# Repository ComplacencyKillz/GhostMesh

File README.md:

---
---
# GhostMesh

**A deployable red-team mesh platform — planted sensors, encrypted command-and-control, line-of-sight control, and a destruct — running on nothing the target owns.**

GhostMesh is a **backpack that snaps onto a Flipper Zero — then detaches and stays in the field.** Attached, it turns your Flipper into a long-range mesh radio: messaging and control over LoRa, no phone, no cell, no internet, nothing the target controls. Detached and planted, it becomes an autonomous node — watching its own perimeter, holding its place on the mesh, and taking orders by line-of-sight IR from you or over the encrypted mesh from your team. Drop it, walk away, and it stays yours.

This repository is the **framework** — the sensing, signaling, and command backbone that offensive capability is built on top of. It reports, it takes commands, and it erases itself on capture. Unlicensed by design.

---

## What's Here

Everything to build one, end to end — all of it open source:

| Deliverable | Location | Status |
|-------------|----------|--------|
| **Operator app** — the Flipper FAP (C99) | [<code>flipper-app/</code>](flipper-app/) | working |
| **Backpack firmware** — custom Heltec Meshtastic modules (C++) | [<code>heltec-firmware/</code>](heltec-firmware/) | working |
| **Board CAD** — the GhostMesh PCB | [<code>kicad/</code>](kicad/) | in progress |
| **Case CAD** — 3D-printable enclosure (FreeCAD) | — | planned |
| **Hardware spec** — every component, datasheet-trackable | [<code>docs/hardware.md</code>](docs/hardware.md) | in progress |
| **Wiring schematic** — the full system, end to end | [<code>kicad/</code>](kicad/) · [<code>docs/wiring.md</code>](docs/wiring.md) | in progress |

The two software halves work today. The board is being designed; the case, the finished component spec, and the whole-system schematic follow it. The transmission — [ghostmesh.info](ghostmesh.info/).

---

## How It Works

The backpack is a **shield.** It plugs onto the Flipper Zero's GPIO header, taps the three pins it needs — TX, RX, GND — and passes the header through to the Heltec and sensor stack riding on top. One board. It runs from its own battery; the Flipper runs from its own. The header is the only link, and it's a link you can break on purpose.

<pre><code>
   ATTACHED — comms terminal            DETACHED — planted node
  ┌──────────────────────┐            ┌──────────────────────┐
  │  backpack             │  pull off  │  backpack             │  ))) mesh → teammate's Flipper
  │  Heltec + sensors     │  ───────▶  │  on its own battery   │
  │ ══ GPIO header ══     │  ◀───────  │  sensing · on mesh    │   ~~ IR → your Flipper
  │  Flipper Zero         │  snap on   │                       │
  └──────────────────────┘            └──────────────────────┘
</code></pre>

**Attached — a comms terminal.** The backpack rides on the Flipper, which drives it over the header link: send and receive over the LoRa mesh, read telemetry, work the Control screen. Your handheld is now a long-range, infrastructure-free field radio.

**Detached — a planted node.** Pull the backpack off. The header disconnects; it keeps running on its own battery as an isolated asset — sensing its surroundings, holding its place on the mesh, waiting.

**Controlled from anywhere.**
- The **original operator** reaches the planted node by **line-of-sight IR** — arm, disarm, or fire the destruct without touching it.
- **Teammates** reach it over the **encrypted LoRa mesh** — status, indicators, wipe, from any Flipper on the private channel.

---

## What Works Today

**Operator terminal — Flipper FAP**
- Send / receive text over the mesh; canned message profiles (3 built-in + up to 5 from SD YAML)
- RX history, RSSI / SNR, marquee display, dated CSV logging (→ KML via <code>tools/log_to_kml.py</code>)
- Live telemetry: temperature / humidity / pressure (BME280), GPS position, battery %
- Menu-hub UI with **Control** (IR arm / disarm / wipe), **encrypted config backup**, and a live **Settings** screen

**Web configurator — [ghostmesh.info/config](https://ghostmesh.info/config)** (Chrome/Edge, USB, no install)
- Live node config over Web Serial (<code>/set</code>/<code>/cfg</code>) — every setting as a slider/toggle
- **Firmware flasher** (esptool-js) — flash the latest build or your own <code>.bin</code> from the browser
- **Payload Upload** — <code>/put</code> chunked file transfer to the node's flash, CRC32-verified

**Backpack — custom Heltec firmware**
- Tamper detection: tilt (moved), photoresistor (case opened), ultrasonic proximity (RCWL-1601, approach)
- Arming gate — sensors report only when armed; flipped by a switch, the mesh, or IR
- Indicators: buzzer, vibration motor, RGB status LED (colors + a green↔red gradient)
- Mesh command CLI — <code>/cmd @target</code>: status, arm/disarm, buzz, vibrate, led, fx, <code>/set</code>/<code>/cfg</code>, <code>/put</code>, wipe
- **Configurable everything**: per-command mesh replies on/off, a <code>silent</code> stealth mode (screen + LEDs + buzzer/vibration off), per-sensor battery gating, GPS/telemetry rate control — all live, no reflash
- IR line-of-sight control (NECext): arm / disarm / the <code>ARM → WIPE → CONFIRM</code> destruct
- Destruct: armed-gated **complete flash erase** — firmware, config, and channel keys wiped to USB download mode; recover by reflash + encrypted-backup restore

**Hardware**
- KiCad schematics for the Flipper and Heltec modules (board layout in progress)

Full phase-by-phase status: [<code>docs/roadmap.md</code>](docs/roadmap.md).

---

## What You Need

The **GhostMesh backpack** — the custom board that integrates all of this into one Flipper shield — is under active development ([<code>kicad/</code>](kicad/)). Until it's fabricated, you build on off-the-shelf parts:

**Core — send / receive over the mesh:**
- Flipper Zero
- Heltec WiFi LoRa 32 V3 (ESP32-S3 + SX1262) + a 915 MHz antenna
- A LiPo for the Heltec (independent of the Flipper battery)
- A PINGEQUA protoboard to seat the Heltec on the Flipper's GPIO header — the dev stand-in for the real board, not the product

**Full backpack — sensing + security:** adds a BME280, a GPS module, tilt / photoresistor / proximity sensors, an IR receiver, a buzzer, a vibration motor, and their driver parts.

The complete bill of materials — every component, GPIO, and driver circuit — is in [<code>docs/hardware.md</code>](docs/hardware.md).

---

## Quick Start

### 1. Flash Meshtastic to the Heltec
Visit [flasher.meshtastic.org](https://flasher.meshtastic.org), select **Heltec WiFi LoRa 32 V3**, flash, and set your region. See [<code>docs/meshtastic-setup.md</code>](docs/meshtastic-setup.md) for the private-channel configuration you'll want before any real use.

### 2. Connect the backpack (three signals)
On the backpack PCB these run through the GPIO header automatically. On the bench, jumper them:
<pre><code>
Flipper U_TX (pin 13)  →  Heltec GPIO7  (Serial module RX)
Flipper U_RX (pin 14)  →  Heltec GPIO6  (Serial module TX)
Flipper GND            →  Heltec GND
</code></pre>
Then configure the Meshtastic **Serial module**: PROTO mode, RX 7, TX 6, 115200, override-console OFF. **Not GPIO43/44** — the CP2102 USB bridge clamps those on battery. **Never bridge the power rails** — the backpack and Flipper each run from their own battery. See [<code>docs/wiring.md</code>](docs/wiring.md).

### 3. Build and install the FAP
<pre><code>
pip install ufbt
cd flipper-app
ufbt
</code></pre>
Copy <code>dist/ghostmesh.fap</code> to <code>SD:/apps/Tools/</code> on the Flipper, or <code>ufbt launch</code> over USB. See [<code>docs/flipper-setup.md</code>](docs/flipper-setup.md).

### 4. (Optional) Build the backpack firmware
The custom Heltec modules build on top of stock Meshtastic. See [<code>heltec-firmware/README.md</code>](heltec-firmware/README.md).

### 5. Run
**Apps → Tools → GhostMesh.** The title bar shows <code>...</code> during the handshake (~3 s), then <code>RDY</code>, then the backpack's battery %. You land on the menu hub — Messages, RX History, Sensors, Control, Status, Backup. See [<code>docs/user-guide.md</code>](docs/user-guide.md).

---

## Documentation

**Start here**
- [<code>docs/overview.md</code>](docs/overview.md) — the system end to end: architecture, concepts, the platform vision

**Build & operate**
- [<code>docs/hardware.md</code>](docs/hardware.md) — full BoM, GPIO allocation, power
- [<code>docs/wiring.md</code>](docs/wiring.md) — pinouts, driver circuits, sensor wiring
- [<code>docs/meshtastic-setup.md</code>](docs/meshtastic-setup.md) — Meshtastic config, private channels
- [<code>docs/flipper-setup.md</code>](docs/flipper-setup.md) — ufbt build & install
- [<code>heltec-firmware/README.md</code>](heltec-firmware/README.md) — building the backpack firmware
- [<code>docs/user-guide.md</code>](docs/user-guide.md) — the FAP, screen by screen

**Operate the backpack**
- [<code>docs/command-cli.md</code>](docs/command-cli.md) — the mesh command CLI + wipe safety
- [<code>docs/opsec.md</code>](docs/opsec.md) — encryption, the destruct, stealth, metadata

**Reference**
- [<code>docs/developer-guide.md</code>](docs/developer-guide.md) — architecture, ISR rules, contributing
- [<code>docs/serial-modes.md</code>](docs/serial-modes.md) — PROTO framing & protobuf field numbers
- [<code>docs/roadmap.md</code>](docs/roadmap.md) — the phased plan (Phases 0–14)
- [<code>docs/red-team-lab-use-cases.md</code>](docs/red-team-lab-use-cases.md) — authorized use cases

---

## License

MIT — see [LICENSE](LICENSE).

<pre><code>
// so light your candles
</code></pre>

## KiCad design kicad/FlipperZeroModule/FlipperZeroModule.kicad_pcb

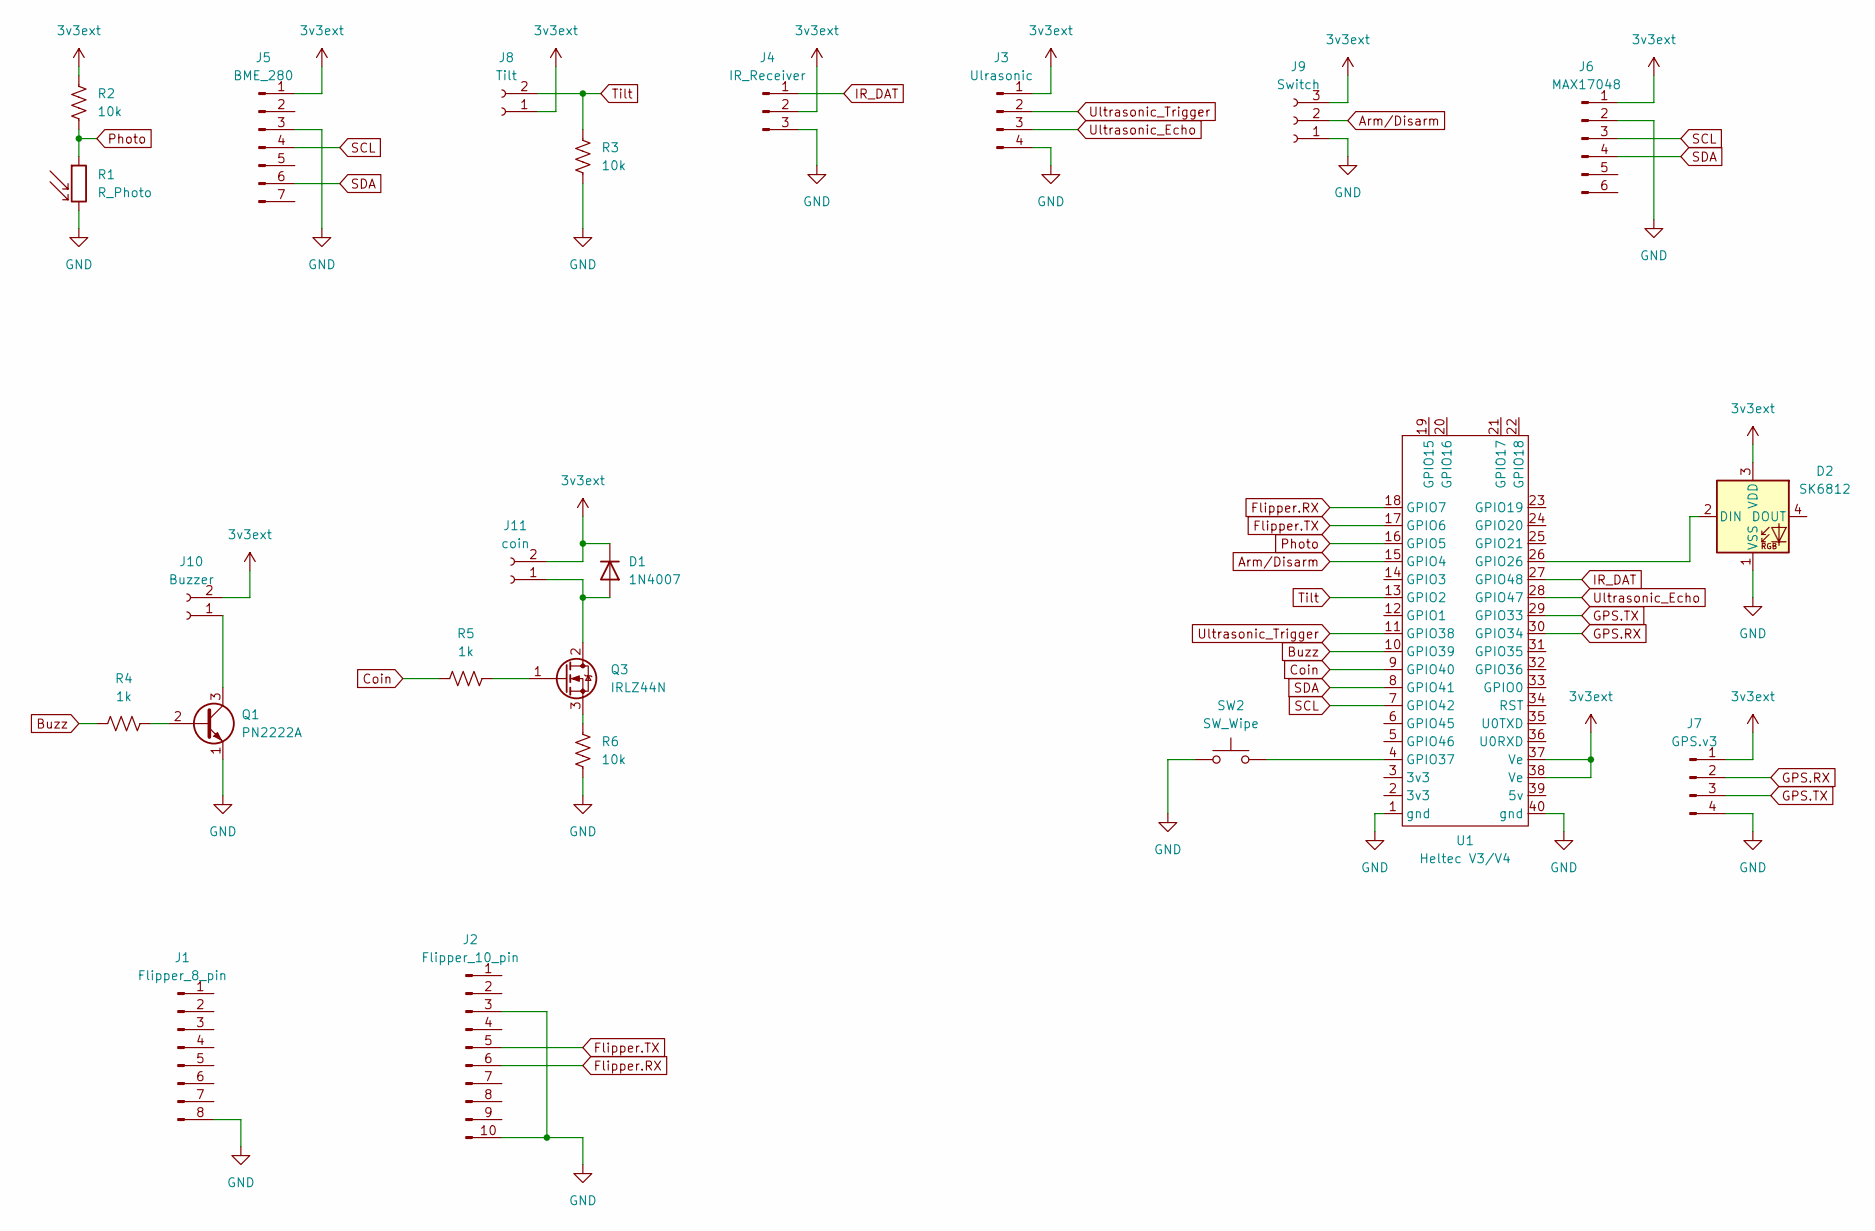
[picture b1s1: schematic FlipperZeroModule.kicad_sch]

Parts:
D1: 1N4007; D_DO-41_SOD81_P10.16mm_Horizontal
D2: SK6812; LED_SK6812_PLCC4_5.0x5.0mm_P3.2mm
J1: Flipper_8_pin; PinHeader_1x08_P2.54mm_Vertical
J2: Flipper_10_pin; PinHeader_1x10_P2.54mm_Vertical
J3: Ulrasonic; PinHeader_1x04_P2.54mm_Vertical
J4: IR_Receiver; PinHeader_1x03_P2.54mm_Vertical
J5: BME_280; PinHeader_1x07_P2.54mm_Vertical
J6: MAX17048; PinHeader_1x06_P2.54mm_Vertical
J7: GPS.v3; PinHeader_1x04_P2.54mm_Vertical
J8: Tilt; PinHeader_1x02_P2.54mm_Vertical
J9: Switch; PinHeader_1x03_P2.54mm_Vertical
J10: Buzzer; PinHeader_1x02_P2.54mm_Vertical
J11: coin; PinHeader_1x02_P2.54mm_Vertical
Q1: PN2222A; TO-92_Inline
Q3: IRLZ44N; TO-220-3_Vertical
R1: R_Photo; R_LDR_5.1x4.3mm_P3.4mm_Vertical
R2, R3, R6: 10k; R_Axial_DIN0207_L6.3mm_D2.5mm_P7.62mm_Horizontal
R4, R5: 1k; R_Axial_DIN0207_L6.3mm_D2.5mm_P7.62mm_Horizontal
SW2: SW_Wipe; SW_PUSH-12mm
U1: Heltec V3/V4; heltech v4

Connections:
3v3ext: D1.1 (K), D2.3 (VDD), J3.1, J4.2, J5.1, J6.1, J7.1, J8.1, J9.3, J10.2, J11.2, R2.1, U1.37 (Ve), U1.38 (Ve)
Arm/Disarm: J9.2, U1.15 (GPIO4)
Buzz: R4.1, U1.10 (GPIO39)
Coin: R5.1, U1.9 (GPIO40)
Flipper.RX: J2.6, U1.18 (GPIO7)
Flipper.TX: J2.5, U1.17 (GPIO6)
GND: D2.1 (VSS), J1.8, J2.3, J2.10, J3.4, J4.3, J5.3, J6.2, J7.4, J9.1, Q1.1 (E), R1.2, R3.2, R6.2, SW2.1, U1.1 (gnd), U1.40 (gnd)
GPS.RX: J7.2, U1.30 (GPIO34)
GPS.TX: J7.3, U1.29 (GPIO33)
IR_DAT: J4.1, U1.27 (GPIO48)
unnamed: D1.2 (A), J11.1, Q3.2 (D)
unnamed: D2.2 (DIN), U1.26 (GPIO26)
unnamed: J10.1, Q1.3 (C)
unnamed: Q1.2 (B), R4.2
unnamed: Q3.1 (G), R5.2
unnamed: Q3.3 (S), R6.1
unnamed: SW2.2, U1.4 (GPIO37)
Photo: R1.1, R2.2, U1.16 (GPIO5)
SCL: J5.4, J6.3, U1.7 (GPIO42)
SDA: J5.6, J6.4, U1.8 (GPIO41)
Tilt: J8.2, R3.1, U1.13 (GPIO2)
Ultrasonic_Echo: J3.3, U1.28 (GPIO47)
Ultrasonic_Trigger: J3.2, U1.11 (GPIO38)

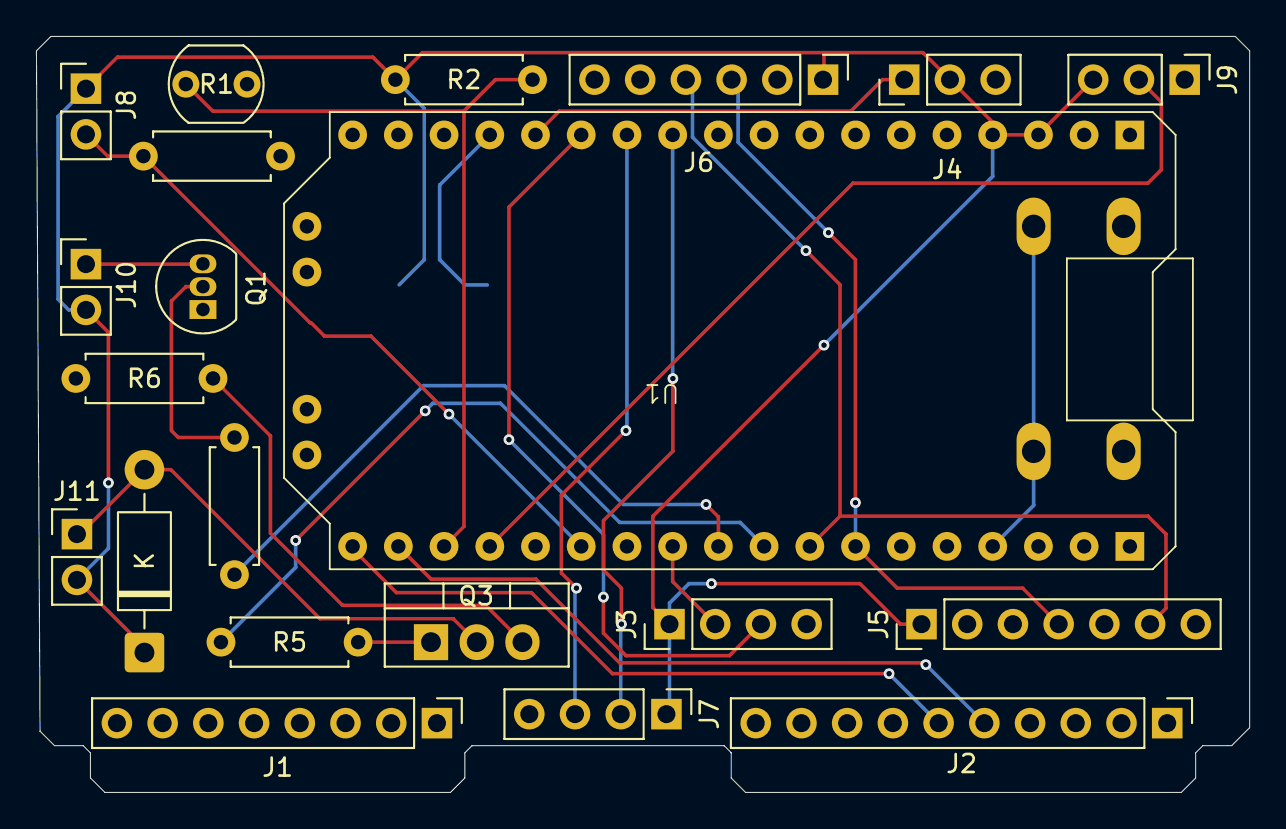
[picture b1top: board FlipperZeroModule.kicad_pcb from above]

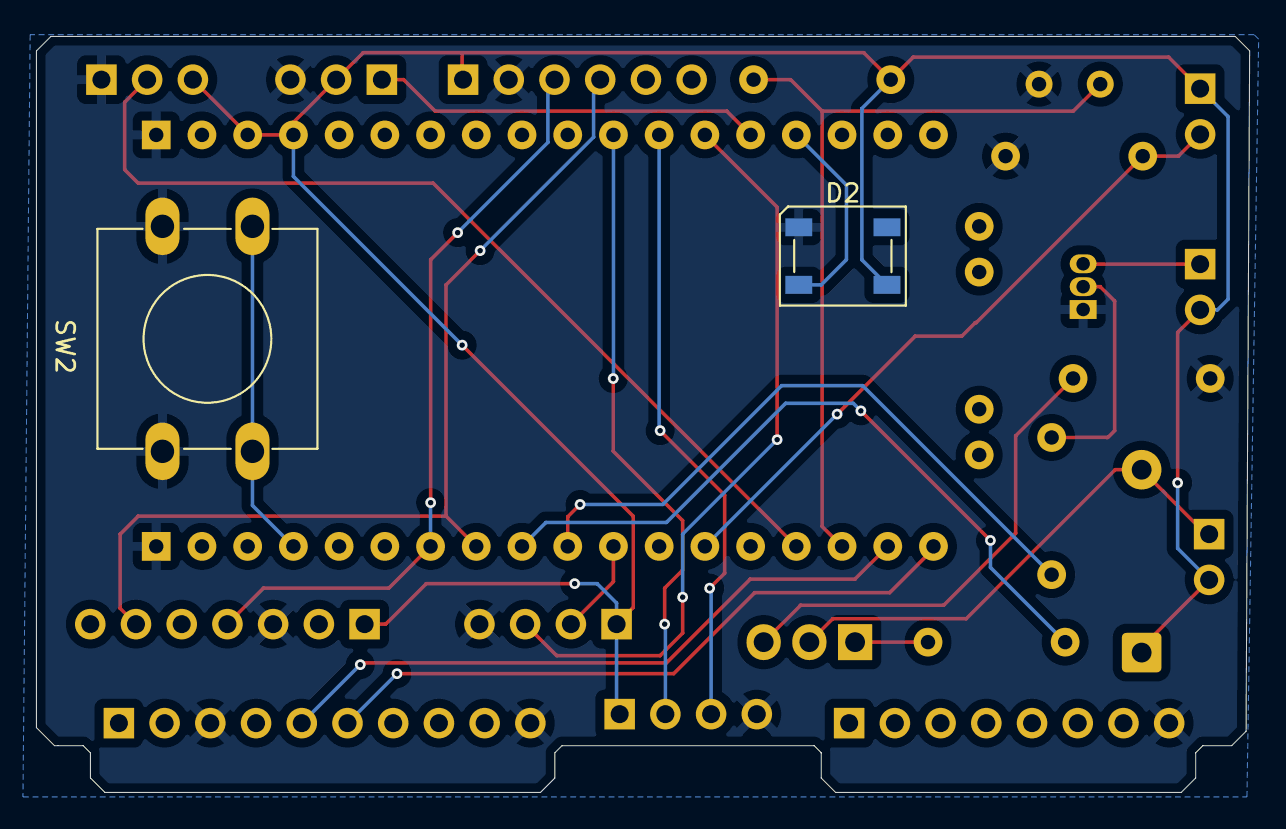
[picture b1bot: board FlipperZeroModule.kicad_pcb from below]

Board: 2 copper layers, 67.4 x 42.0 mm, 23 parts (2 on the bottom side), 23 nets.

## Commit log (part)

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2026-05-03 feat: initial GhostMesh v0.1 — Flipper Zero Meshtastic companion
    Phase 0 (docs) and Phase 1 (UART byte-counter FAP) complete.
    - application.fam + ghostmesh.c: compilable FAP entry point, UART open,
    RX/TX byte counters, OK sends CHECKIN OK over TEXTMSG serial mode
    - uart_helper: USART1 (pins 13/14) init, async RX callback, TX with flush
    - textmsg_mode: plain-text send helper for Meshtastic TEXTMSG serial mode
    - main_view: ViewPort-based status display (UART active, RX/TX counts)
2026-05-05 fix: correct GPIO pin assignments and update validated wiring docs
    Hardware validation complete — two Heltec V3 nodes communicating over
    LoRa mesh with Flipper Zero as UART controller.
    - application.fam: remove invalid fap_name param (broke ufbt build)
    - docs/wiring.md: fix GPIO7 label typo (was showing "38"), add confirmed
    GPIO pin status table from boot log analysis, add verified test results
    - docs/meshtastic-setup.md: replace PuTTY verify section with Python
2026-05-05 feat: Phase 2 — canned message selector with scrollable menu
    Replaces the byte-counter display with a navigable message list.
    - UP/DOWN scrolls through 10 canned messages (hold for repeat)
    - OK sends selected message over UART -> Meshtastic -> LoRa mesh
    - 2-second "Sent: <msg>" feedback on status bar after sending
    - Incoming mesh text lines accumulated from UART RX and shown on
    status bar once data arrives
2026-05-05 feat: Phase 3 — profile selector with SD card custom messages
    App now opens on a profile selection screen before the message list.
    - Three built-in profiles: Grid Down, Hiking / SAR, Red Team
    - Each profile has its own 8-message set appropriate to the scenario
    - OK on profile screen loads that profile's messages and enters the
    message list; BACK from message list returns to profile selector
    - SD card support: if /ext/apps_data/ghostmesh/custom.txt exists,
2026-05-06 fix: correct all protobuf field numbers for PROTO mode
    Field numbers confirmed from meshtastic Python library (2.7.8).
    All previous encodings used wrong field numbers causing silent drops.
    Encoder (proto_encode_text / send):
    MeshPacket.to field 2 fixed32 (was field 3 varint)
    MeshPacket.hop_limit field 9 (was field 13)
    Decoder (FromRadio / receive):
2026-05-06 docs: update wiring to confirmed GPIO44/43 (PhoneAPI on UART0)
    Final confirmed wiring: Flipper TX -> GPIO44 (Heltec "RX" pad, UART0 RX),
    Flipper RX -> GPIO43 (Heltec "TX" pad, UART0 TX).
    GhostMesh talks directly to Meshtastic's PhoneAPI on UART0, bypassing
    the SerialModule entirely. No special Meshtastic serial module config
    needed. This is the same path as the official meshtastic Python library.
    TX and RX both confirmed working 2026-05-05.
2026-05-06 feat: YAML profile loader, repo cleanup, docs rewrite
    YAML profile loader:
    - Single file: SD:/apps_data/ghostmesh/profiles.yaml
    - Up to 5 custom profiles alongside 3 built-ins (8 total)
    - Parser handles name:/- syntax, comments, blank lines, unknown keys
    - Input validation: printable ASCII only, length caps, quote stripping,
    empty profiles and messages silently discarded
2026-05-06 docs: rewrite hardware.md and uart-test-plan.md to reflect PROTO/GPIO44 reality
2026-05-06 fix: revert ISR-unsafe mutex from RX callback
    furi_mutex_acquire cannot be called from the UART ISR callback context.
    The MED-1 non-blocking acquire was silently dropping every received
    message. Reverted to direct write with volatile rx_updated, which is
    the correct ISR-safe pattern on Cortex-M4.
2026-05-06 docs: document ISR callback constraint in proto_notes
    Explains why volatile is used instead of a mutex for rx_updated,
    and why furi_mutex_acquire must not be called from the UART RX
    callback chain.
2026-05-06 feat: phase 4 — SD logging, RSSI/SNR, history screen, horizontal scroll
    SD card logging:
    - Decode MeshPacket.rx_rssi (field 12) and rx_snr (field 8) via
    extended ProtoRxCallback signature
    - log_manager appends to /ext/apps_data/ghostmesh/log_YYYYMMDD.csv
    with timestamp, node_id, message, rssi, snr; header on first create
    RX history screen:
2026-05-06 feat: phase 4 — SD logging, RSSI/SNR, history screen, marquee scroll
    SD card logging:
    - Decode MeshPacket.rx_rssi (field 12) and rx_snr (field 8)
    - log_manager appends to /ext/apps_data/ghostmesh/log_YYYYMMDD.csv
    RX history screen:
    - Long-press Down on message screen opens 16-entry history (newest
    first) showing sender, dBm, and full message; BACK returns
2026-05-06 docs: expand roadmap phases 6-14, full hardware BOM and sensor wiring
    roadmap.md:
    - Phases 6-14 detailed: security baseline, env telemetry, GPS/wardriving,
    battery intelligence, physical controls, dead-drop surveillance, SIGINT,
    remote payloads, UART encryption
    - Architecture notes: dual UART, dual I2C bus, hybrid PROTO/ASCII protocol,
    custom firmware requirement matrix
2026-05-06 docs: backpack-first architecture — sensors on Heltec, controls on Flipper
    The Heltec backpack operates fully unattended at a dead drop. All tamper
    and proximity sensors live on the Heltec (GPIO2 tilt, GPIO4 slide switch,
    GPIO5 photoresistor, GPIO21/47 HC-SR04, GPIO48 IR receiver) and are driven
    by custom Meshtastic modules that broadcast alerts over LoRa with no Flipper
    present. The Flipper ProtoBoard carries only operator controls: arming gate
    slide switch, buzzer, and vibration motor.
2026-05-07 docs: full documentation push — user guide, developer guide, opsec, updates
    New docs:
    - docs/user-guide.md: screen-by-screen user manual (profile/message/history
    screens, navigation, CSV logging, KML, custom profiles, RSSI reference)
    - docs/developer-guide.md: architecture, ISR constraints, PROTO encode/decode,
    UI system, marquee logic, phase conventions, Heltec module system overview
    - docs/opsec.md: encryption picture, private channel setup, UART risk, nuke
2026-05-07 docs: Afternow reference, updated voice skill, website skill, gitignore
    - ghostmesh.info/docs/afternow-reference.md: full Tales from the Afternow
    research — verbatim quotes, complete universe vocabulary, political framing,
    Librarian voice guide, relevance to both GhostMesh and ComplacencyKillz
    - .claude/skills/brand_voice_and_content_tone/SKILL.md: extended with
    Afternow universe context — ServerMonk identity, corpopolitical framing,
    Librarian speech patterns, verbatim phrases for direct use, vocabulary list,
2026-05-07 fix: pin vite to ^7 to satisfy Astro compatibility requirement
2026-05-07 feat: video background, audio unlock, two-stage splash interaction
    - Add ghostmesh_a 4K background video (H.264, 4.3MB — re-encoded from
    30MB 4K original at CRF 33 for web delivery)
    - Splash now gates on first user interaction (any key or click) before
    typing begins — this gesture is the browser audio unlock required to
    play video with sound
    - Stage 1: blinking "PRESS ANY KEY TO RECEIVE TRANSMISSION" prompt
2026-05-07 fix: scattered DVD menu layout matching complacencykillz pattern
    - Menu items are now position:absolute, scattered asymmetrically across
    the screen (top-right cluster, bottom-left cluster) — not centered
    - Each item has a ::before radial-gradient + backdrop-filter:blur(12px)
    fog that makes labels readable over the video background
    - Title block (GHOSTMESH) absolutely positioned top-left, large
    - Vignette overlay darkens edges to improve contrast
2026-05-07 fix: rounded fog corners, faster splash+entrance, lighter canvas
    - border-radius on ::before fog boxes (rounded corners)
    - Typewriter speed: 16ms → 6ms per char; inter-line gaps cut from
    100ms→40ms, post-sl4 pause 500ms→180ms; total splash typing time
    drops from ~9s to ~3s
    - Entrance animation durations: 0.35→0.25s, delays tightened
    - Mesh canvas node count: 12→7 to reduce GPU competition with 4K video
2026-05-07 feat: audio on sub-pages + return prompt + sessionStorage skip
    Sub-pages: video starts muted (required for autoplay), unmutes to
    volume 0.2 on first user interaction (click or keypress) — quieter
    than main page (0.35). No prompt needed, unlocks seamlessly.
    Main page: sessionStorage flag set on first ACKNOWLEDGE. Return visits
    show in-character prompt instead of full splash:
    "SIGNAL INTERRUPTED — You are leaving the transmission.
2026-05-07 feat: chapter intros on sub-pages, welcome back on return, no sub-page audio
    Main page return prompt rewritten in voice:
    "SIGNAL RESTORED / The node held your position.
    // connection re-established / [ RESUME TRANSMISSION ]"
    Single button — the click IS the audio unlock. No STAY option.
    Sub-page chapter intros (visible before content, dismiss to reveal):
    - INITIALIZE SYSTEM: "What you are about to read was not authorized. It was transmitted anyway."
2026-05-07 fix: deploy to / not /null/, chapter intro visible text colors, referrer return prompt
    deploy.sh: yq returns literal "null" for empty YAML values, bypassing the
    :-/ default and deploying every build to /null/ while web root stayed stale.
    Fixed by checking for "null" and converting to empty string so the default / applies.
    Chapter intro text colors: --text-ghost (#1a2540) on black background was
    invisible. Fixed: header → --red, lines → --text (#c8d4e8).
    Return prompt: switched from sessionStorage to document.referrer check.
2026-05-07 fix: bfcache Back button — pageshow restores return prompt and video
    The browser Back button uses bfcache which restores page state without
    re-running JS, leaving the video paused and the return prompt hidden.
    pageshow handler (fires on bfcache restore): sets fromBfcache flag,
    calls video.play(), shows return prompt.
    confirmBtn handler moved outside isReturn block so it's always wired.
    On confirm: hides (not removes) return prompt so bfcache can show it
2026-05-07 fix: content clipping, sys-bar tickers, REC placement
    - body overflow:hidden so content never bleeds past sys-bar lines
    - scene-panel and mobile dvd-menu fixed between top/bottom bars
    - REC indicator moved into top sys-bar (path left, REC right)
    - back links lowered to clear corner bracket (top: 3rem / 4.2rem)
    - bottom sys-bar split into two scrolling half-tickers: project
    text marquee on left, timestamp right-aligned on right
2026-05-25 feat: mesh canvas on sub-pages, scrolling sys-bar, title scramble effects
    - Add animated mesh canvas to SubLayout matching main page texture
    - Replace static sys-bar top label with scrolling ticker on both pages
    - Add scramble reveal effect for GHOSTMESH title on entrance
    - Add character-swap glitch effects (G flip, E→3, O→0, S→5, T→7)
    - Replace mobile-only flex layout with dynamic scatter↔stack transition
    driven by viewport ratio, with smooth GSAP animation on resize
2026-05-25 docs: add CLAUDE.md with full project context for Claude Code
